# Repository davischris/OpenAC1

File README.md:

# OpenAC1

This work is largely based on the work of Tor-Eirik Bakke Lunde (https://github.com/tebl/RC6502-Apple-1-Replica).  I really liked his project and I had just read "Apple 1 Replica Creation: Back to the Garage" by Tom Owad, so I was very interested in making a "workalike" Apple 1.

I wanted to extend this project to include USB keyboard and VGA monitor support, as well as the ability to read programs from an SD card.

This project also includes code from other open source projects including Geoff Graham's VT100 Teminal Emulator (https://geoffg.net/terminal.html) including David Hansel's modification to use a USB keyboard.

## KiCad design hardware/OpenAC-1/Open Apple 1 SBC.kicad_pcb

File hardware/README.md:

Schematic and circuit board were designed in KiCAD 6.0

ROM image should be burned to an AT28C64 EEPROM

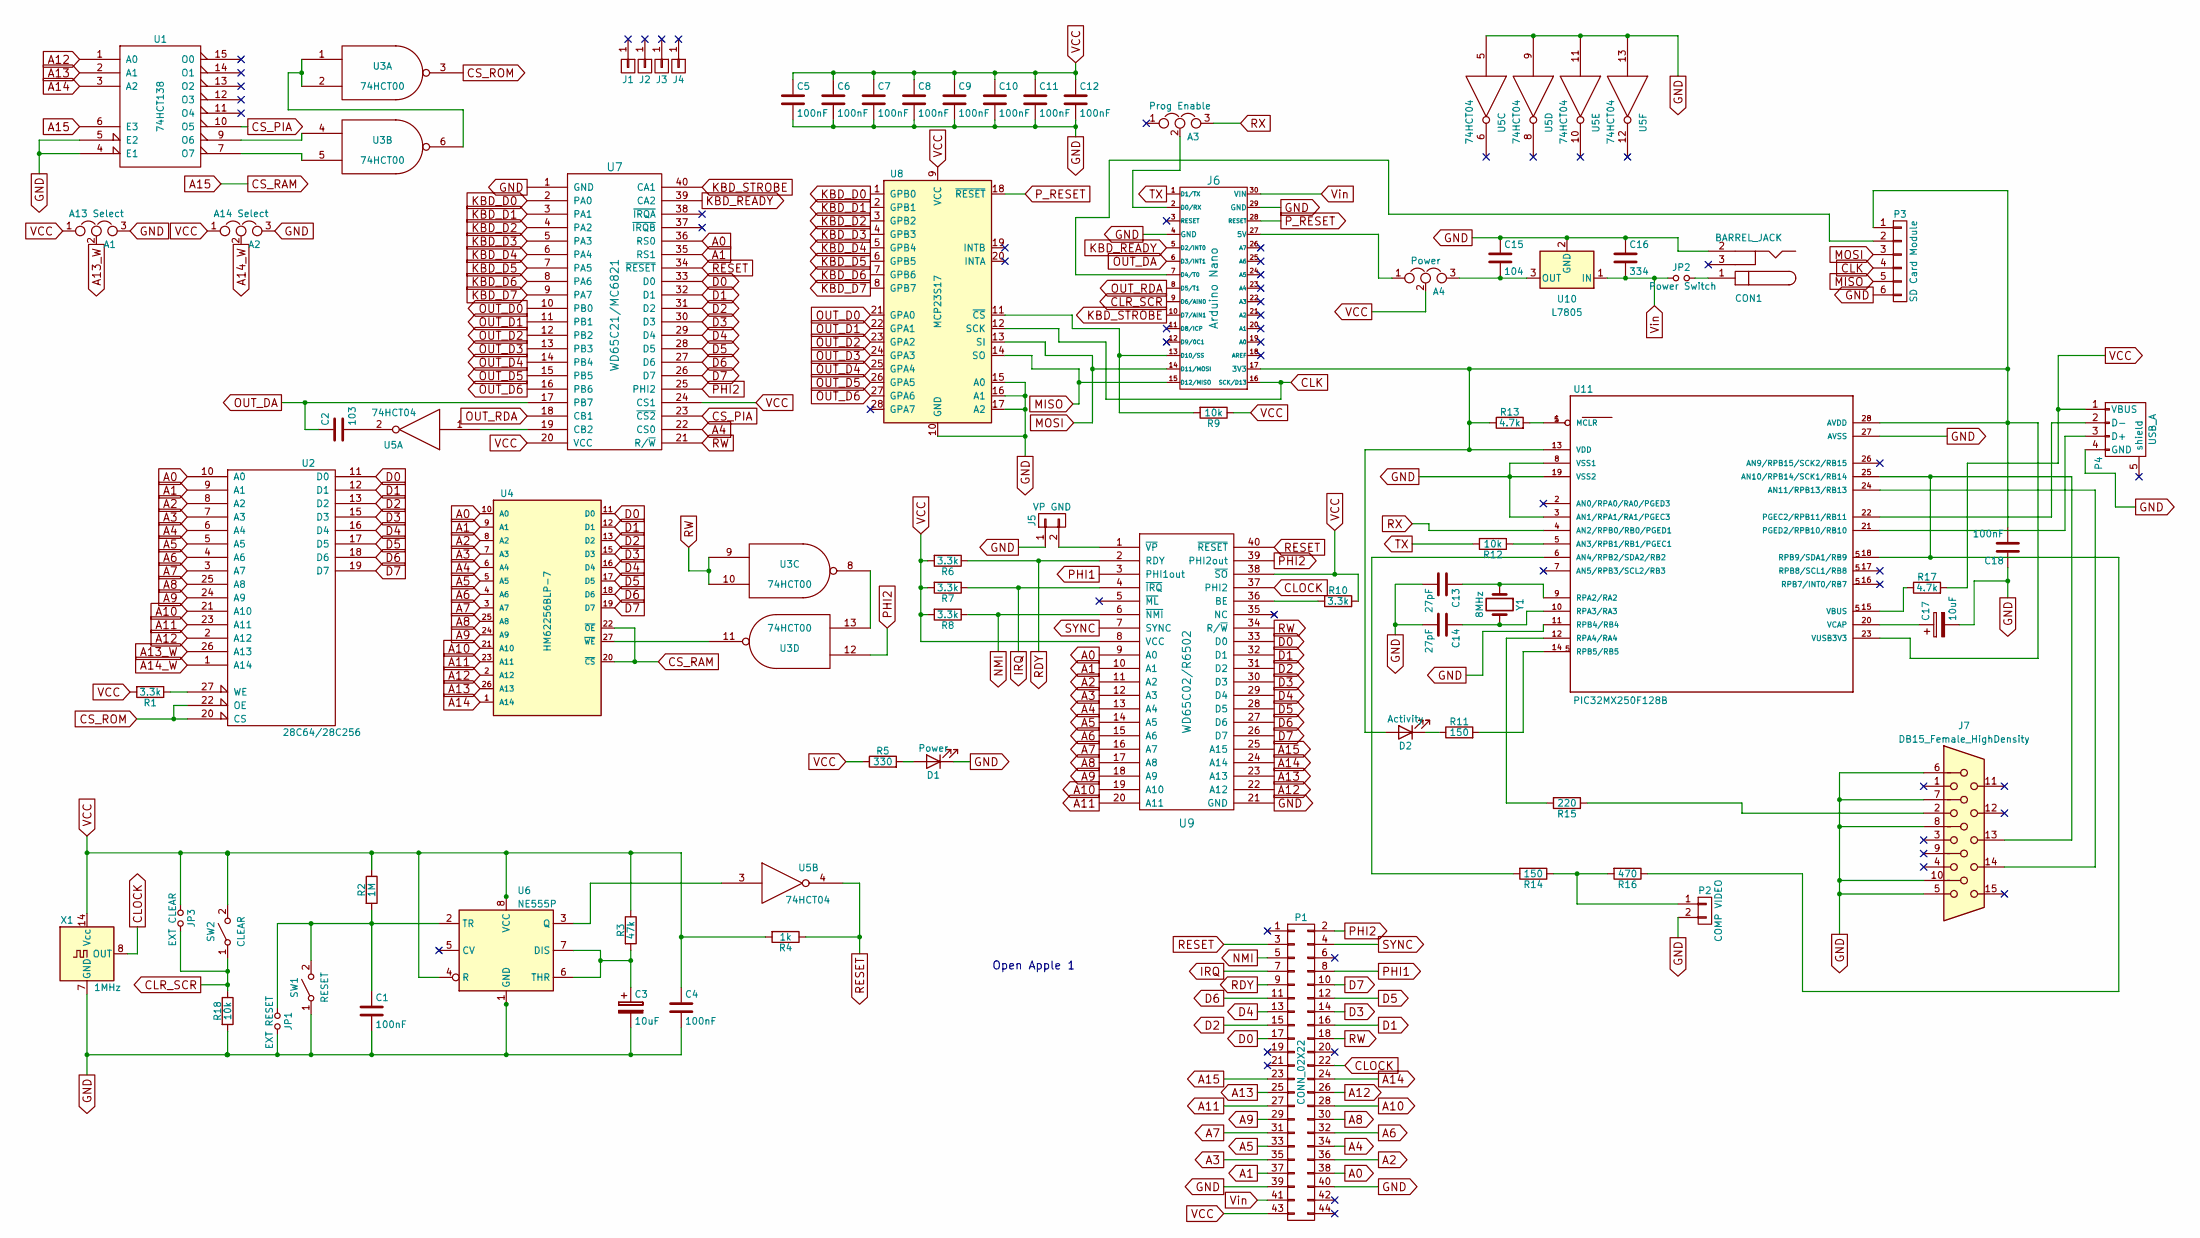
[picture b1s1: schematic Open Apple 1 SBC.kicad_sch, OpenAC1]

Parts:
A1: A13 Select; PinHeader_1x03_P2.54mm_Vertical
A2: A14 Select; PinHeader_1x03_P2.54mm_Vertical
A3: Prog Enable; PinHeader_1x03_P2.54mm_Vertical
A4: Power; PinHeader_1x03_P2.54mm_Vertical
C1, C4, C5, C6, C7, C8, C9, C10, C11, C12, C18: 100nF; C_Disc_D3.8mm_W2.6mm_P2.50mm
C2: 103; C_Disc_D4.3mm_W1.9mm_P5.00mm
C3, C17: 10uF; CP_Radial_D4.0mm_P2.00mm
C13, C14: 27pF; C_Disc_D3.8mm_W2.6mm_P2.50mm
C15: 104; C_Disc_D4.3mm_W1.9mm_P5.00mm
C16: 334; C_Disc_D4.3mm_W1.9mm_P5.00mm
CON1: BARREL_JACK; BarrelJack_Horizontal
D1: Power; LED_D5.0mm
D2: Activity; LED_D5.0mm
J1, J2, J3, J4: Hole; Mounting
J5: VP GND; PinHeader_1x02_P2.54mm_Vertical
J6: Arduino Nano; Arduino_Nano
J7: DB15_Female_HighDensity; DSUB-15-HD_Female_Horizontal_P2.29x1.98mm_EdgePinOffset3.03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
JP1: EXT RESET; PinHeader_1x02_P2.54mm_Vertical
JP2: Power Switch; PinHeader_1x02_P2.54mm_Vertical
JP3: EXT CLEAR; PinHeader_1x02_P2.54mm_Vertical
P1: CONN_02X22; PinHeader_2x22_P2.54mm_Vertical
P2: COMP VIDEO; PinHeader_1x02_P2.54mm_Vertical
P3: SD Card Module; PinHeader_1x06_P2.54mm_Vertical
P4: USB_A
R1, R6, R7, R8, R10: 3.3k; R_Axial_DIN0207_L6.3mm_D2.5mm_P10.16mm_Horizontal
R2: 1M; R_Axial_DIN0207_L6.3mm_D2.5mm_P10.16mm_Horizontal
R3: 47k; R_Axial_DIN0207_L6.3mm_D2.5mm_P10.16mm_Horizontal
R4: 1k; R_Axial_DIN0207_L6.3mm_D2.5mm_P10.16mm_Horizontal
R5: 330; R_Axial_DIN0207_L6.3mm_D2.5mm_P10.16mm_Horizontal
R9, R12, R18: 10k; R_Axial_DIN0207_L6.3mm_D2.5mm_P10.16mm_Horizontal
R11, R14: 150; R_Axial_DIN0207_L6.3mm_D2.5mm_P10.16mm_Horizontal
R13, R17: 4.7k; R_Axial_DIN0207_L6.3mm_D2.5mm_P10.16mm_Horizontal
R15: 220; R_Axial_DIN0207_L6.3mm_D2.5mm_P10.16mm_Horizontal
R16: 470; R_Axial_DIN0207_L6.3mm_D2.5mm_P10.16mm_Horizontal
SW1: RESET; SW_PUSH_6mm
SW2: CLEAR; SW_PUSH_6mm
U1: 74HCT138; DIP-16_W7.62mm
U2: 28C64/28C256; DIP-28_W15.24mm
U3: 74HCT00; DIP-14_W7.62mm
U4: HM62256BLP-7; DIP-28_W15.24mm
U5: 74HCT04; DIP-14_W7.62mm
U6: NE555P; DIP-8_W7.62mm
U7: WD65C21/MC6821; DIP-40_W15.24mm
U8: MCP23S17; DIP-28_W7.62mm
U9: WD65C02/R6502; DIP-40_W15.24mm
U10: L7805; TO-220-3_Vertical
U11: PIC32MX250F128B; DIP-28_W7.62mm
X1: 1MHz; Oscillator_DIP-14
Y1: 8MHz; Crystal_HC49-U_Vertical

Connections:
A0: P1.38, U2.10 (A0), U4.10 (A0), U7.36 (RS0), U9.9 (A0)
A1: P1.37, U2.9 (A1), U4.9 (A1), U7.35 (RS1), U9.10 (A1)
A2: P1.36, U2.8 (A2), U4.8 (A2), U9.11 (A2)
A3: P1.35, U2.7 (A3), U4.7 (A3), U9.12 (A3)
A4: P1.34, U2.6 (A4), U4.6 (A4), U7.22 (CS0), U9.13 (A4)
A5: P1.33, U2.5 (A5), U4.5 (A5), U9.14 (A5)
A6: P1.32, U2.4 (A6), U4.4 (A6), U9.15 (A6)
A7: P1.31, U2.3 (A7), U4.3 (A7), U9.16 (A7)
A8: P1.30, U2.25 (A8), U4.25 (A8), U9.17 (A8)
A9: P1.29, U2.24 (A9), U4.24 (A9), U9.18 (A9)
A10: P1.28, U2.21 (A10), U4.21 (A10), U9.19 (A10)
A11: P1.27, U2.23 (A11), U4.23 (A11), U9.20 (A11)
A12: P1.26, U1.1 (A0), U2.2 (A12), U4.2 (A12), U9.22 (A12)
A13: P1.25, U1.2 (A1), U4.26 (A13), U9.23 (A13)
A13_W: A1.2, U2.26 (A13)
A14: P1.24, U1.3 (A2), U4.1 (A14), U9.24 (A14)
A14_W: A2.2, U2.1 (A14)
A15: P1.23, U1.6 (E3), U4.20 (~CS), U4.22 (~OE), U9.25 (A15)
CLK: J6.16 (SCK/D13), P3.4, U8.12 (SCK)
CLOCK: P1.22, U9.37 (PHI2), X1.8 (OUT)
CLR_SCR: J6.9 (D6/AIN0), JP3.2, R18.1, SW2.1 (A)
CS_PIA: U1.10 (O5), U7.23 (~CS2)
CS_ROM: U2.20 (CS), U2.22 (OE), U3.3
D0: P1.17, U2.11 (D0), U4.11 (D0), U7.33 (D0), U9.33 (D0)
D1: P1.16, U2.12 (D1), U4.12 (D1), U7.32 (D1), U9.32 (D1)
D2: P1.15, U2.13 (D2), U4.13 (D2), U7.31 (D2), U9.31 (D2)
D3: P1.14, U2.15 (D3), U4.15 (D3), U7.30 (D3), U9.30 (D3)
D4: P1.13, U2.16 (D4), U4.16 (D4), U7.29 (D4), U9.29 (D4)
D5: P1.12, U2.17 (D5), U4.17 (D5), U7.28 (D5), U9.28 (D5)
D6: P1.11, U2.18 (D6), U4.18 (D6), U7.27 (D6), U9.27 (D6)
D7: P1.10, U2.19 (D7), U4.19 (D7), U7.26 (D7), U9.26 (D7)
GND: A1.3, A2.3, C1.2, C3.2, C4.2, C5.2, C6.2, C7.2, C8.2, C9.2, C10.2, C11.2, C12.2, C13.2, C14.2, C15.1, C16.1, C17.2, C18.1, CON1.2, D1.1 (K), J5.1, J6.4 (GND), J6.29 (GND), J7.5, J7.6, J7.7, J7.8, J7.10, JP1.2, P1.39, P1.40, P2.2, P3.6, P4.4 (GND), R18.2, SW1.1 (A), U1.4 (E1), U1.5 (E2), U1.8 (GND), U2.14 (GND), U3.7 (GND), U4.14 (GND), U5.5, U5.7 (GND), U5.9, U5.11, U5.13, U6.1 (GND), U7.1 (GND), U8.10 (GND), U8.15 (A0), U8.16 (A1), U8.17 (A2), U9.21 (GND), U10.2 (GND), U11.3 (AN1/RPA1/RA1/PGEC3), U11.8 (VSS1), U11.11 (RPB4/RB4), U11.19 (VSS2), U11.27 (AVSS), X1.7 (GND)
IRQ: P1.7, R7.1, U9.4 (~IRQ)
KBD_D0: U7.2 (PA0), U8.1 (GPB0)
KBD_D1: U7.3 (PA1), U8.2 (GPB1)
KBD_D2: U7.4 (PA2), U8.3 (GPB2)
KBD_D3: U7.5 (PA3), U8.4 (GPB3)
KBD_D4: U7.6 (PA4), U8.5 (GPB4)
KBD_D5: U7.7 (PA5), U8.6 (GPB5)
KBD_D6: U7.8 (PA6), U8.7 (GPB6)
KBD_D7: U7.9 (PA7), U8.8 (GPB7)
KBD_READY: J6.5 (D2/INT0), U7.39 (CA2)
KBD_STROBE: J6.10 (D7/AIN1), U7.40 (CA1)
MISO: J6.15 (D12/MISO), P3.5, U8.14 (SO)
MOSI: J6.14 (D11/MOSI), P3.3, U8.13 (SI)
NMI: P1.5, R8.1, U9.6 (~NMI)
unnamed: A3.2, J6.2 (D0/RX)
unnamed: A4.1, J6.27 (5V)
unnamed: A4.3, C15.2, U10.3 (OUT)
unnamed: C1.1, JP1.1, R2.2, SW1.2 (B), U6.2 (TR)
unnamed: C2.2, U5.2
unnamed: C3.1, R3.2, U6.6 (THR), U6.7 (DIS)
unnamed: C13.1, U11.9 (RPA2/RA2), Y1.1
unnamed: C14.1, U11.10 (RPA3/RA3), Y1.2
unnamed: C17.1, U11.20 (VCAP)
unnamed: C18.2, D2.2 (A), J6.17 (3V3), P3.1, R13.1, U11.13 (VDD), U11.23 (VUSB3V3), U11.28 (AVDD)
unnamed: CON1.1, JP2.2
unnamed: D1.2 (A), R5.2
unnamed: D2.1 (K), R11.1
unnamed: J5.2, U9.1 (~VP)
unnamed: J6.7 (D4/T0), P3.2
unnamed: J6.13 (D10/SS), R9.2, U8.11 (~CS)
unnamed: J7.2, R15.1
unnamed: J7.13, R16.1, U11.18 (RPB9/SDA1/RB9), U11.25 (AN10/RPB14/SCK1/RB14)
unnamed: J7.14, U11.24 (AN11/RPB13/RB13)
unnamed: P2.1, R14.1, R16.2
unnamed: P4.2 (D-), U11.22 (PGEC2/RPB11/RB11)
unnamed: P4.3 (D+), U11.21 (PGED2/RPB10/RB10)
unnamed: R1.1, U2.27 (WE)
unnamed: R10.1, U9.36 (BE)
unnamed: R11.2, U11.14 (RPB5/RB5)
unnamed: R12.1, U11.5 (AN3/RPB1/RB1/PGEC1)
unnamed: R13.2, U11.1 (MCLR)
unnamed: R14.2, U11.6 (AN4/RPB2/SDA2/RB2)
unnamed: R15.2, U11.12 (RPA4/RA4)
unnamed: R17.1, U11.15 (VBUS)
unnamed: U1.7 (O7), U3.5
unnamed: U1.9 (O6), U3.4
unnamed: U3.1, U3.2, U3.6
unnamed: U3.11, U4.27 (~WE)
unnamed: U3.8, U3.13
unnamed: U5.1, U7.19 (CB2)
unnamed: U5.3, U6.3 (Q)
OUT_D0: U7.10 (PB0), U8.21 (GPA0)
OUT_D1: U7.11 (PB1), U8.22 (GPA1)
OUT_D2: U7.12 (PB2), U8.23 (GPA2)
OUT_D3: U7.13 (PB3), U8.24 (GPA3)
OUT_D4: U7.14 (PB4), U8.25 (GPA4)
OUT_D5: U7.15 (PB5), U8.26 (GPA5)
OUT_D6: U7.16 (PB6), U8.27 (GPA6)
OUT_DA: C2.1, J6.6 (D3/INT1), U7.17 (PB7)
OUT_RDA: J6.8 (D5/T1), U7.18 (CB1)
PHI1: P1.8, U9.3 (PHI1out)
PHI2: P1.2, U3.12, U7.25 (PHI2), U9.39 (PHI2out)
P_RESET: J6.28 (RESET), U8.18 (~RESET)
RDY: P1.9, R6.1, U9.2 (RDY)
RESET: P1.3, R4.1, U5.4, U7.34 (~RESET), U9.40 (~RESET)
RW: P1.18, U3.9, U3.10, U7.21 (R/~W), U9.34 (R/~W)
RX: A3.3, U11.4 (AN2/RPB0/RB0/PGED1)
SYNC: P1.4, U9.7 (SYNC)
TX: J6.1 (D1/TX), R12.2
VCC: A1.1, A2.1, A4.2, C4.1, C5.1, C6.1, C7.1, C8.1, C9.1, C10.1, C11.1, C12.1, JP3.1, P1.43, P4.1 (VBUS), R1.2, R2.1, R3.1, R4.2, R5.1, R6.2, R7.2, R8.2, R9.1, R10.2, R17.2, SW2.2 (B), U1.16 (VCC), U2.28 (VCC), U3.14 (VCC), U4.28 (VCC), U5.14 (VCC), U6.4 (R), U6.8 (VCC), U7.20 (VCC), U7.24 (CS1), U8.9 (VCC), U9.8 (VCC), U9.38 (~SO), X1.14 (Vcc)
Vin: C16.2, J6.30 (VIN), JP2.1, P1.41, U10.1 (IN)

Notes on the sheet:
Open Apple 1

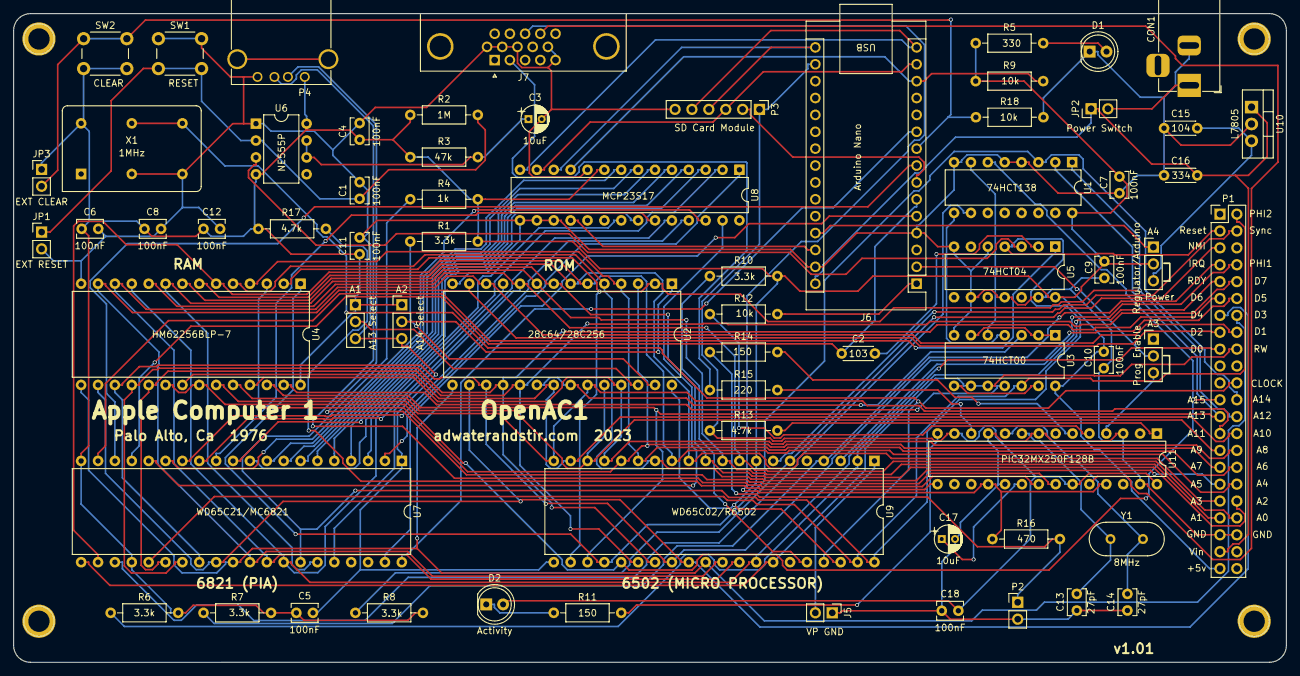
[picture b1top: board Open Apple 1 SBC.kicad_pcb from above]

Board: 2 copper layers, 191.5 x 97.6 mm, 72 parts (0 on the bottom side), 103 nets.

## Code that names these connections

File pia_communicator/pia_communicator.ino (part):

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#define VIDEO_DA 3

#define IO_KBD 1
#define IO_KBD_D0 8
#define IO_KBD_D6 14
#define IO_KBD_DA 15
#define KBD_READY 2
#define KBD_STROBE 7    //was 4, needed to free up for sd module
#define LED 13
#define CLRSCR 6

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}

void configure_pins() {
  pinMode(KBD_READY, INPUT);
  pinMode(VIDEO_DA, INPUT);
  pinMode(KBD_STROBE, OUTPUT);
  pinMode(VIDEO_RDA, OUTPUT);

  // initialize the button pin as a input:
  pinMode(CLRSCR, INPUT);

  /* Test the use of interrupts for communication with the PIA */
  attachInterrupt(digitalPinToInterrupt(KBD_READY), on_keyboard_data_ack, FALLING);
  attachInterrupt(digitalPinToInterrupt(VIDEO_DA), on_video_data_ready, RISING);
}

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  }

  /* Wait for PIA to acknowledge this.
    -> We are waiting for a falling edge on the KBD_READY pin.
    -> Once this occurs the keyboard_data_sent_ok flag will be set in the interrupt
  */
  uint32_t t_send = millis();
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
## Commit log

2023-10-16 Update pia_communicator.ino
    Remove cause of most repeating characters
2024-01-08 Add modified source files
2024-01-08 Add KiCad Project
2024-01-08 Add ROM image
2024-01-08 Add README
